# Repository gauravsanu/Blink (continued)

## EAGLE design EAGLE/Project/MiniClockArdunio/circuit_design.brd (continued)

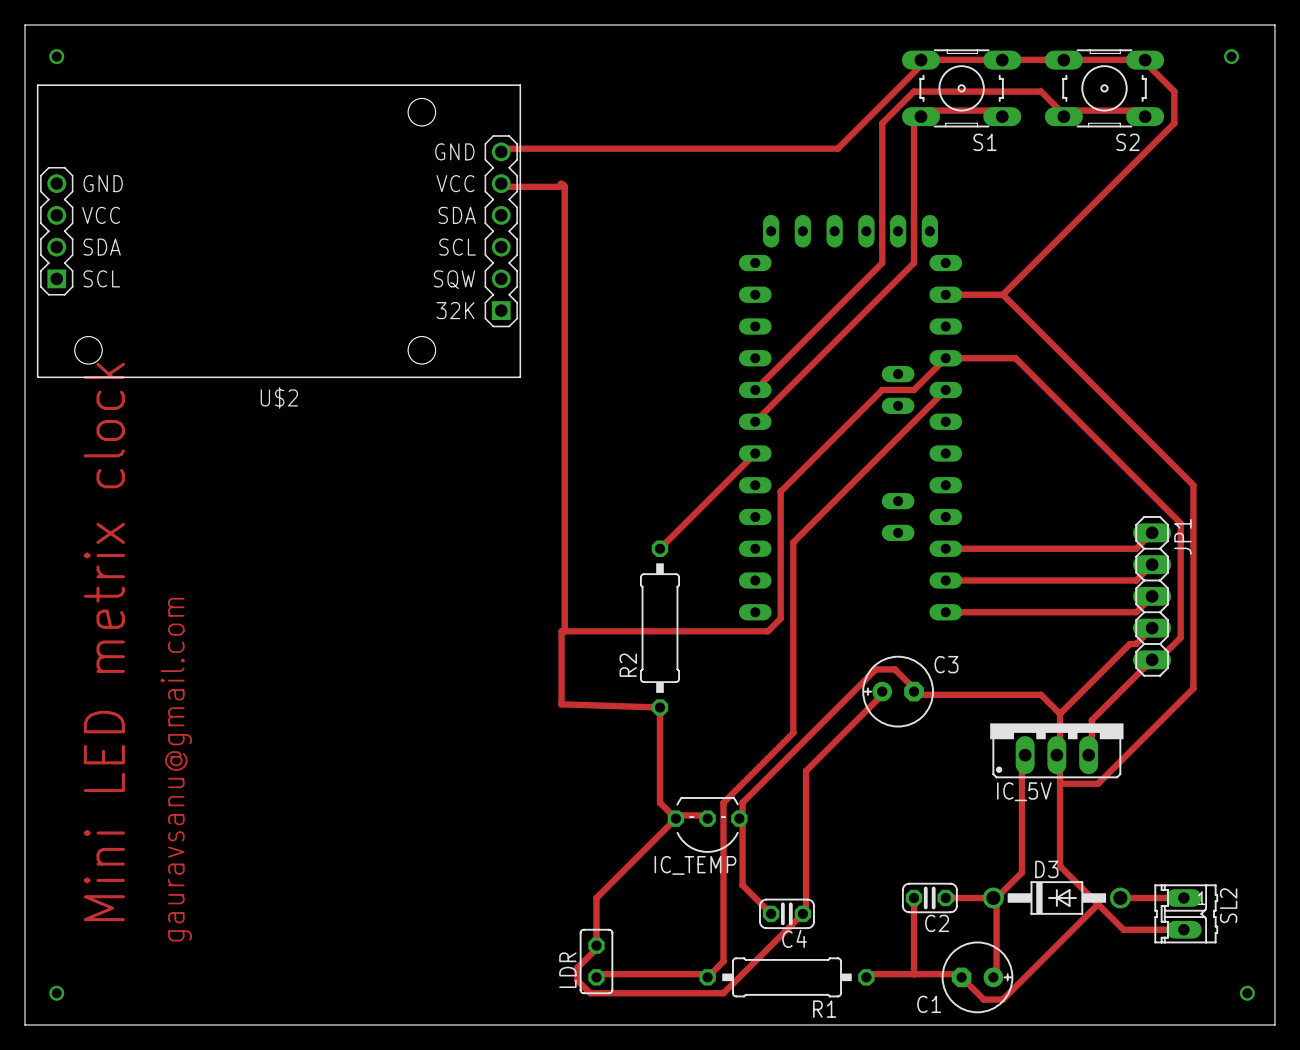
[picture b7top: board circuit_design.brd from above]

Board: 2 copper layers, 100.0 x 80.0 mm, 17 parts (0 on the bottom side), 11 nets.

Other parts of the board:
DRILEGEND: DRILEGEND

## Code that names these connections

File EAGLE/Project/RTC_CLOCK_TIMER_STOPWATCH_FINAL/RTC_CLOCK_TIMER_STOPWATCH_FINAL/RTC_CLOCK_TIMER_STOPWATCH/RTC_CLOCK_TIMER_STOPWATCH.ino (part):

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int temp,inc,hours1,minut,add=11,temp1=3,mode=0;
int tSeconds=0, tMinutes=0, hours=0;  //this line, along with another line in void timerFunction(), is where you can adjust the amount of time that is counted down in                                                                    //the timer function
int centiseconds=0, sSeconds=0, sMinutes=0;
int next=A0;   
int INC=A1;
int set_mad=A2;
int shw_dat=A3;
int buzzer=11;
int HOUR,MINUT,SECOND=0;
dht DHT;

#define DHT11_PIN 10
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RTC.begin();
lcd.begin(16,2);
pinMode(INC, INPUT);
pinMode(next, INPUT);
pinMode(set_mad, INPUT);
pinMode(shw_dat, INPUT);
pinMode(buzzer, OUTPUT);
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      HOUR++;
      if(HOUR==24)
      {
       HOUR=0;
      }
      while(digitalRead(INC)==0);
     }
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}
void timerFunction()  //the timer function was made with the help of this post: http://pastebin.com/f57045830
{
  int set=0;
    lcd.setCursor(4,1);
    //lcd.setCursor(0, 1);
    lcd.print("00:00:00");
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
                   while(digitalRead(shw_dat)==1)
                    {
                      set=1;
                   if(digitalRead(set_mad)==0)  //if "Start/Stop" is pressed, the timer counts down
                      {
                        tSeconds++;
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                {
              while(digitalRead(shw_dat) == 1)  //the alarm will only go off until "Restart" is pressed
              {
                set=2;
                lcd.setCursor(4, 1);
                lcd.print("00:00:00");
                for(int i=0;i<5;i++)
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  }
  if(digitalRead(shw_dat) == 0 && set==2)
               {
                set=0;
                mode=0;
                break;
                }
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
